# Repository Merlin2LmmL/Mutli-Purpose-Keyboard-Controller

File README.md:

# Mutli-Purpose-Keyboard-Controller

## Idea
I thought about what multi purpose Device could be usefull in my day to day life. Then ive got the idea to maybe build a stream deck kinda thing. But i didnt see a world, in which i would actively use that, but it would still be neat to have something like that. Then a wired controller came to my mind. I thought, that that was a great idea too. I also wanted to build like a small handheld console aswell. Then I thought about how cool it would be to have all those things in one. And that was the final outcome. This Device can switch modes from a steam deck, to a simple wired, handheld controller, that you can play games with on your pc and also a standalone console (as long as you give it power). 

## Hardware

I carefully picked Hardware Parts that would be cheap, but also fulfill the projects main idea and make it fun to use. 
#### Buttons
For the Buttons I chose keyboard buttons, because I thought they would give the Device a nice look and would make it feel like it actually was useable as a stream deck unlike if i would have used real controller Buttons. I also decided on a Middle Button for mode switching.
#### Joystick
I could have just kept 4 Buttons for Movement in minigames, that would later be played on the Device but I liked the idea of a seperate Joystick way better. It also balances the controller and makes it more symetrical.
#### LEDs
The LEDs I picked only for stylistic reasons. They could indicte in which mode the Device currently is in Binary (to allow for 4 modes) or maybe just indicate weather the device is active or recieved inputs.
#### OLED Display
I picked a screen last, because it would be the most expensive thing on the list, but i thought about how many new funtionalitys it would bring. It allows for a 128x64px display, which is able to show full on mini games. So i figured it'd be worth it.

## Design Files
### 3D Model
(.STEP file is STILL at "3d Model/Joy_Controller.step")
This is the finsihed Model of the entire Device. Only the key caps are missing but it'd make no real difference to add them in here anyway. See how the Controller still looks retro style while having plenty of functionality? I also lerned from previous designe flaws. that the hole for the usb c port must be big enough.

This Picture shows the inside of the Device. I wanted to keep everything modular and open. Thats why the display is very easily unpluggable aswell as the Joystick.

### PCB
For the Schematic I inspired myself by the Hackpad from https://blueprint.hackclub.com/hackpad/index.md and added a horizontal 4 pin header for the joystick and a 5 pin header for the display. I first searched for a fitting Oled display and only then connected the correct pins because I found out, that they were no all pined out the same way.

I first settled on the form of the device when I designed the actual PC. It all came together quite nicely. I later added the display and figured, that it could go above the rp2040 so i added the header above it.

## Software
### Modes
I decided on the following 3 modes:
#### Stream Deck
Press Buttons for quick actions such as copy/paste, activate a macro or activate an LED Strip around my desk, that is powered by my PC via USB A.
#### Controller
Control movement in any game on my PC, Laptop, Tablet or really any USB Keyboard-supported Device.
#### Console
Play games such as Tetris, Snake, etc. on the Device, powered by the RP2040 just by powering it using for example a power bank for quick play to go.
### To be continued
Well, for now i cant really show much more here until i actually build this thing. But thats not gonna be a real issue, since ive made some good experience with python, if you look at my profile.

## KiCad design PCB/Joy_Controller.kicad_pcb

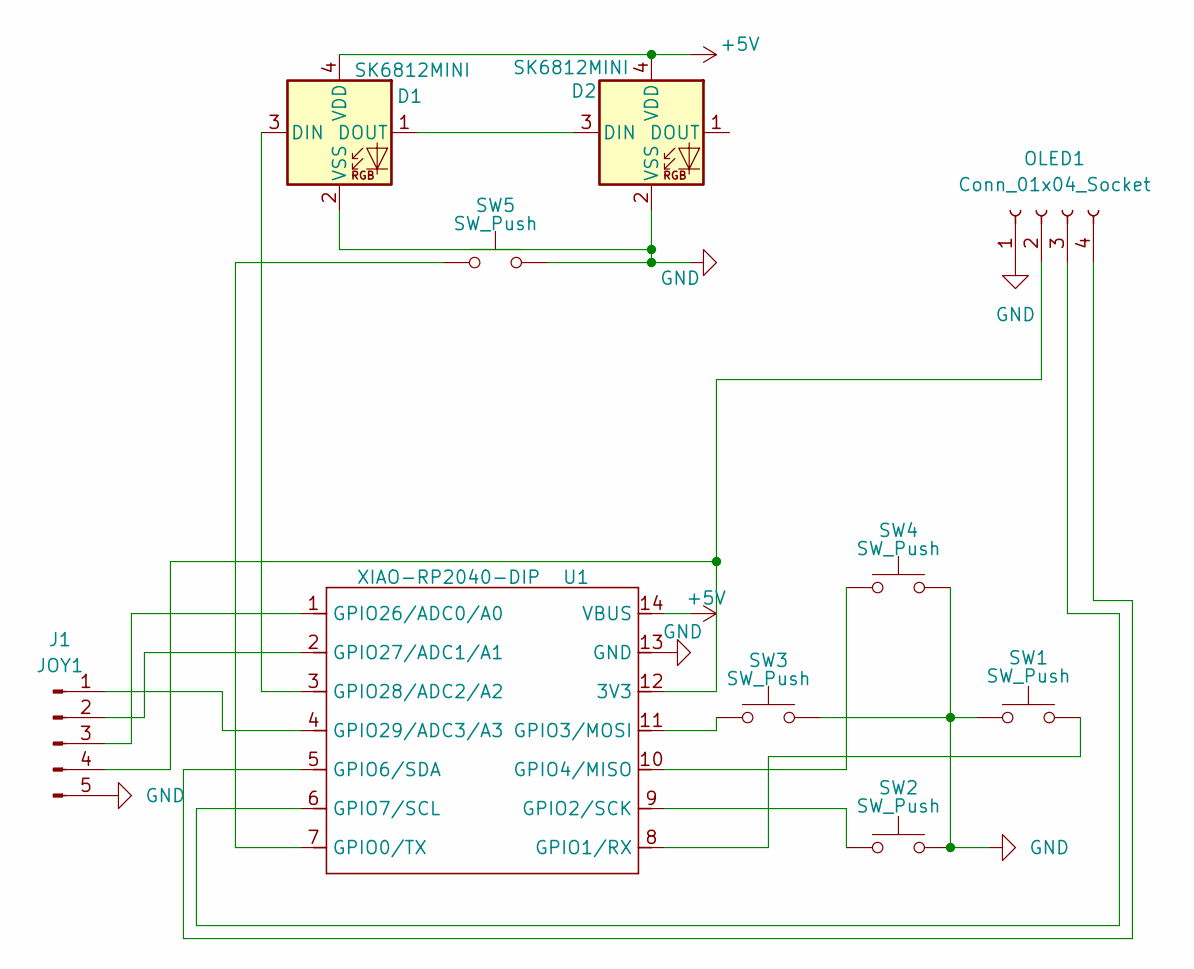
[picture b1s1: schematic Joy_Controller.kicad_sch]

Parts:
D1, D2: SK6812MINI; LED_SK6812MINI_PLCC4_3.5x3.5mm_P1.75mm
J1: JOY1; PinSocket_1x05_P2.54mm_Horizontal
OLED1: Conn_01x04_Socket; PinSocket_1x04_P2.54mm_Vertical
SW1, SW2, SW3, SW4, SW5: SW_Push; SW_Cherry_MX_1.00u_PCB
U1: XIAO-RP2040-DIP; MOUDLE14P-XIAO-DIP-SMD

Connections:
+5V: D1.4 (VDD), D2.4 (VDD), U1.14 (VBUS)
GND: D1.2 (VSS), D2.2 (VSS), J1.5, OLED1.1, SW1.1, SW2.2, SW3.2, SW4.2, SW5.2, U1.13 (GND)
unnamed: D1.3 (DIN), U1.3 (GPIO28/ADC2/A2)
unnamed: D1.1 (DOUT), D2.3 (DIN)
unnamed: J1.1, U1.4 (GPIO29/ADC3/A3)
unnamed: J1.2, U1.2 (GPIO27/ADC1/A1)
unnamed: J1.3, U1.1 (GPIO26/ADC0/A0)
unnamed: J1.4, OLED1.2, U1.12 (3V3)
unnamed: OLED1.3, U1.6 (GPIO7/SCL)
unnamed: OLED1.4, U1.5 (GPIO6/SDA)
unnamed: SW5.1, U1.7 (GPIO0/TX)
unnamed: SW1.2, U1.8 (GPIO1/RX)
unnamed: SW2.1, U1.9 (GPIO2/SCK)
unnamed: SW3.1, U1.11 (GPIO3/MOSI)
unnamed: SW4.1, U1.10 (GPIO4/MISO)

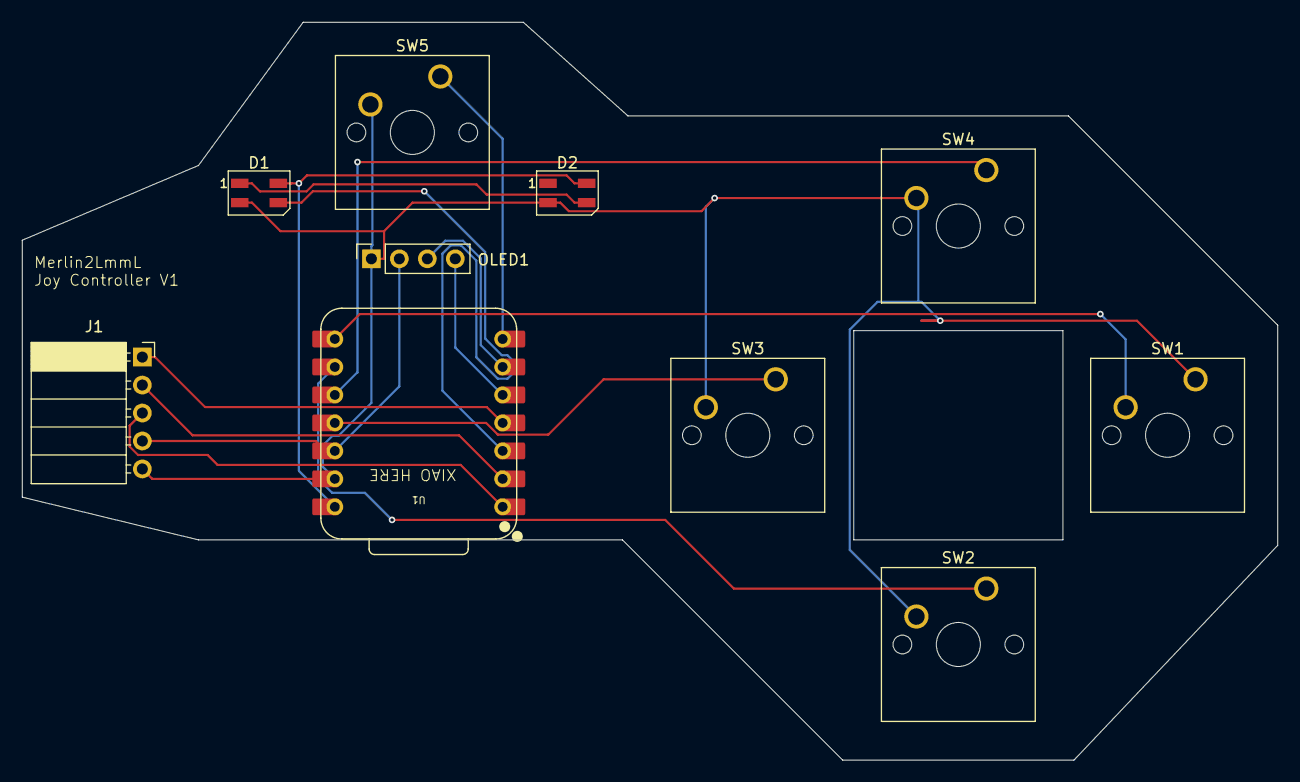
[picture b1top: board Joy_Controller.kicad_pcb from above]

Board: 2 copper layers, 114.0 x 67.0 mm, 10 parts (0 on the bottom side), 15 nets.

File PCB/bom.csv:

Designator,Footprint,Quantity,Value,LCSC Part #
"D1, D2",LED_SK6812MINI_PLCC4_3.5x3.5mm_P1.75mm,2,SK6812MINI,
J1,PinSocket_1x05_P2.54mm_Horizontal,1,JOY1,
OLED1,PinSocket_1x04_P2.54mm_Vertical,1,Conn_01x04_Socket,
"SW1, SW2, SW3, SW4, SW5",SW_Cherry_MX_1.00u_PCB,5,SW_Push,
U1,XIAO-RP2040-DIP,1,XIAO-RP2040-DIP,

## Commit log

2026-01-02 Added Files
    Added Fusion and other different 3d printing files as well as the PCB files.
2026-01-02 Added OLED Screen and changed Tracks on PCB
    A OLED Screen was searched and found. The PCB was accordingly updated and the 3d model aswell.
2026-01-03 Reorganized Repo and fixed Overlapping
2026-01-03 Enhance README with project details and descriptions
    Expanded the README with detailed sections on the device's idea, hardware components, design files, PCB design, and software modes.
2026-01-03 Added BOM
2026-01-03 Added Screwholes
2026-01-03 Update README with .STEP file info
    Added note about the .STEP file location and corrected typos.
